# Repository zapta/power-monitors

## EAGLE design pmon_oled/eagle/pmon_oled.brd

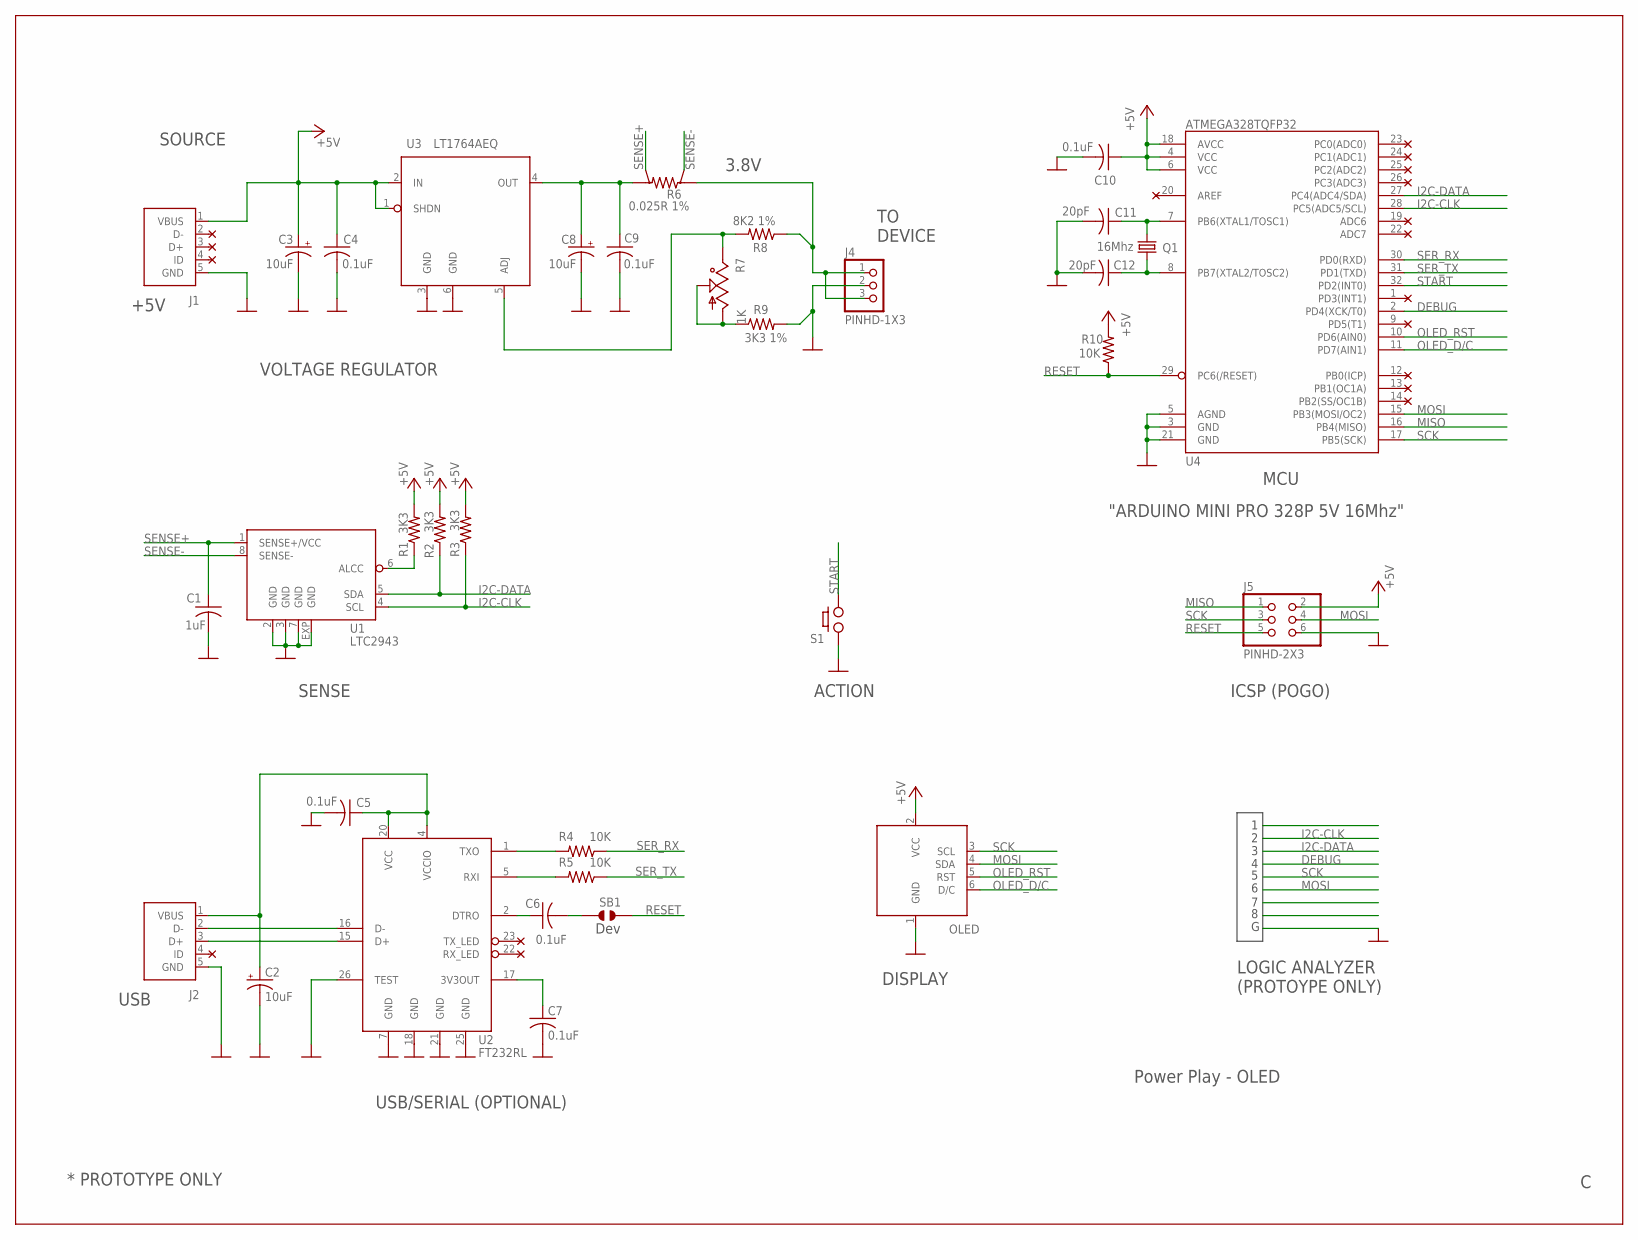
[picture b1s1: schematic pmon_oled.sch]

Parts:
C1: 1uF; C0603
C2, C3, C8: 10uF; A/3216-18R
C4, C5, C6, C7, C9, C10: 0.1uF; C0603
C11, C12: 20pF; C0603
J1, J2: USB; USB-MICRO-ZX62RD-AB-5P8
J4: PINHD-1X3; 1X03
J5: PINHD-2X3; 2X03
OLED: OLED
Q1: 16Mhz; CRYSTAL-CTS406
R1, R2, R3: 3K3; R0603
R4, R5, R10: 10K; R0603
R6: 0.025R 1%; KELVIN-6432
R7: 1K; TRIM-POT_SM-42/43A
R8: 8K2 1%; R0603
R9: 3K3 1%; R0603
S1: PUSH_BUTTON; TLE1105
SB1: JUMPER_SOLDER_1X2
U1: LTC2943; DFN8-3X3
U2: FT232RL; SSOP28DB
U3: LT1764AEQ; TO263-5
U4: ATMEGA328TQFP32; TQFP32-08

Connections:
+5V: C3.+, C4.1, C10.1, J1.1 (VBUS), J5.2, OLED.2 (VCC), R1.2, R2.2, R3.2, R10.2, U3.1 (SHDN), U3.2 (IN), U4.4 (VCC), U4.6 (VCC), U4.18 (AVCC)
DEBUG: U4.2 (PD4(XCK/T0))
GND: C1.2, C2.-, C3.-, C4.2, C5.2, C7.2, C8.-, C9.2, C10.2, C11.2, C12.2, J1.5 (GND), J2.5 (GND), J4.2, J5.6, OLED.1 (GND), R9.2, S1.A (1), U1.2 (GND), U1.3 (GND), U1.7 (GND), U1.EXP (GND), U2.7 (GND), U2.18 (GND), U2.21 (GND), U2.25 (GND), U2.26 (TEST), U3.3 (GND), U3.6 (GND), U4.3 (GND), U4.5 (AGND), U4.21 (GND)
I2C-CLK: R3.1, U1.4 (SCL), U4.28 (PC5(ADC5/SCL))
I2C-DATA: R2.1, U1.5 (SDA), U4.27 (PC4(ADC4/SDA))
MISO: J5.1, U4.16 (PB4(MISO))
MOSI: J5.4, OLED.4 (SDA), U4.15 (PB3(MOSI/OC2))
unnamed: R1.1, U1.6 (ALCC)
unnamed: C11.1, Q1.1, U4.7 (PB6(XTAL1/TOSC1))
unnamed: R4.2, U2.1 (TXO)
unnamed: C12.1, Q1.3 (2), U4.8 (PB7(XTAL2/TOSC2))
unnamed: R5.2, U2.5 (RXI)
unnamed: C8.+, C9.1, R6.I2, U3.4 (OUT)
unnamed: J2.3 (D+), U2.15 (D+)
unnamed: C6.1, U2.2 (DTRO)
unnamed: C6.2, SB1.1
unnamed: J2.2 (D-), U2.16 (D-)
unnamed: C7.1, U2.17 (3V3OUT)
unnamed: R7.1, R7.2, R9.1
unnamed: R7.3, R8.2, U3.5 (ADJ)
unnamed: J4.1, J4.3, R6.I1, R8.1
OLED_D/C: OLED.6 (D/C), U4.11 (PD7(AIN1))
OLED_RST: OLED.5 (RST), U4.10 (PD6(AIN0))
RESET: J5.5, R10.1, SB1.2, U4.29 (PC6(/RESET))
SCK: J5.3, OLED.3 (SCL), U4.17 (PB5(SCK))
SENSE+: C1.1, R6.V2, U1.1 (SENSE+/VCC)
SENSE-: R6.V1, U1.8 (SENSE-)
SER_RX: R4.1, U4.30 (PD0(RXD))
SER_TX: R5.1, U4.31 (PD1(TXD))
START: S1.B (2), U4.32 (PD2(INT0))
VUSB: C2.+, C5.1, J2.1 (VBUS), U2.4 (VCCIO), U2.20 (VCC)

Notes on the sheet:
USB/SERIAL (OPTIONAL)
ICSP (POGO)
MCU
Power Play - OLED
SENSE
VOLTAGE REGULATOR
+5V
LOGIC ANALYZER (PROTOYPE ONLY)
USB
TO DEVICE
3.8V
* PROTOTYPE ONLY
"ARDUINO MINI PRO 328P 5V 16Mhz"
ACTION
SOURCE
DISPLAY
Dev

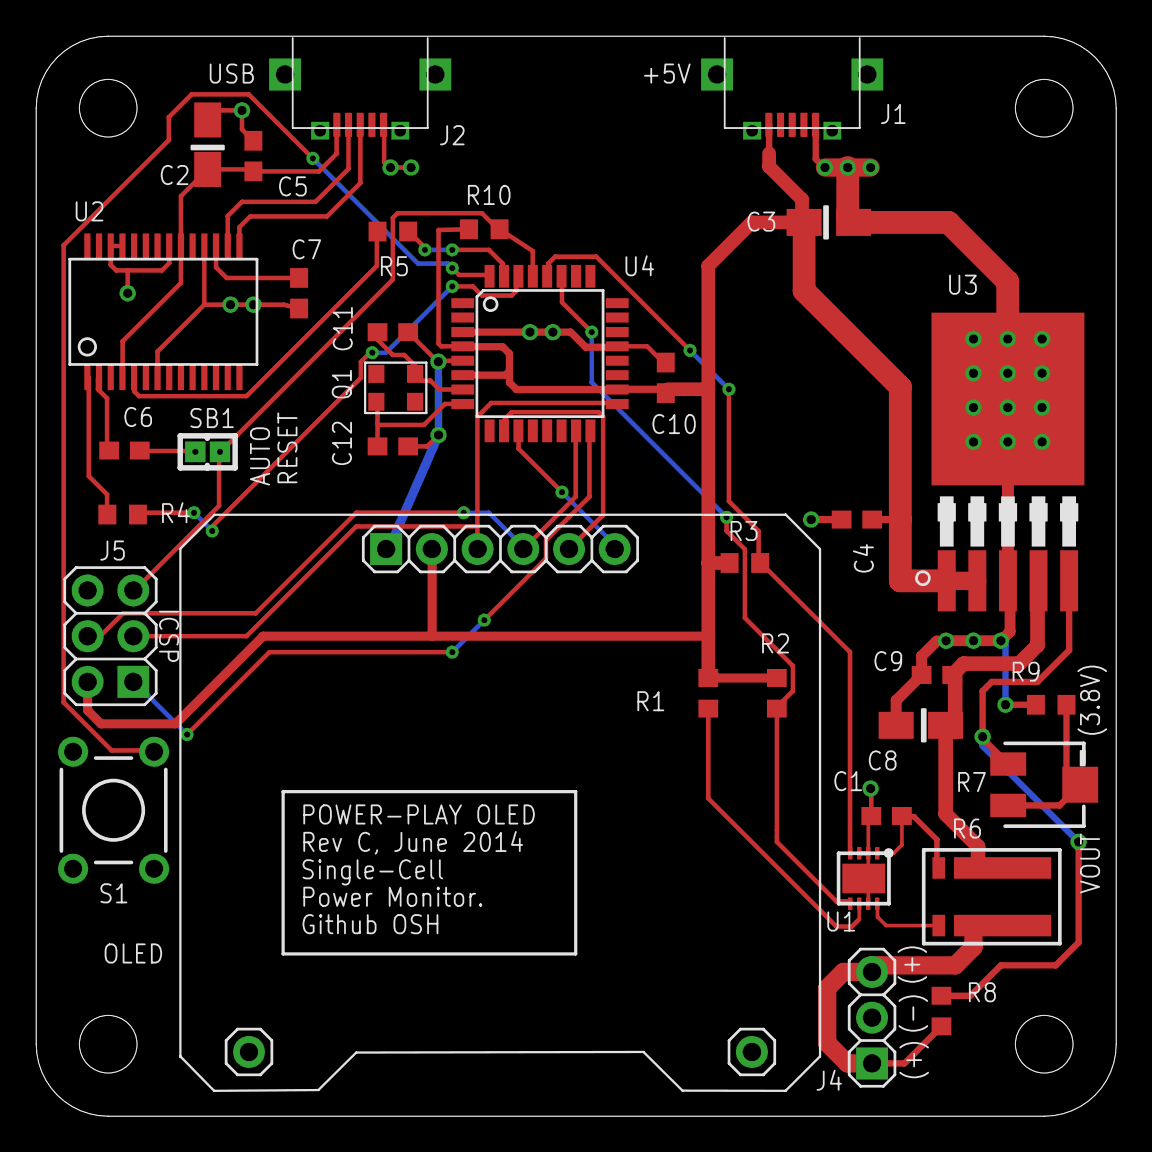
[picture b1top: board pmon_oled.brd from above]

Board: 2 copper layers, 60.0 x 60.0 mm, 34 parts (0 on the bottom side), 30 nets.
